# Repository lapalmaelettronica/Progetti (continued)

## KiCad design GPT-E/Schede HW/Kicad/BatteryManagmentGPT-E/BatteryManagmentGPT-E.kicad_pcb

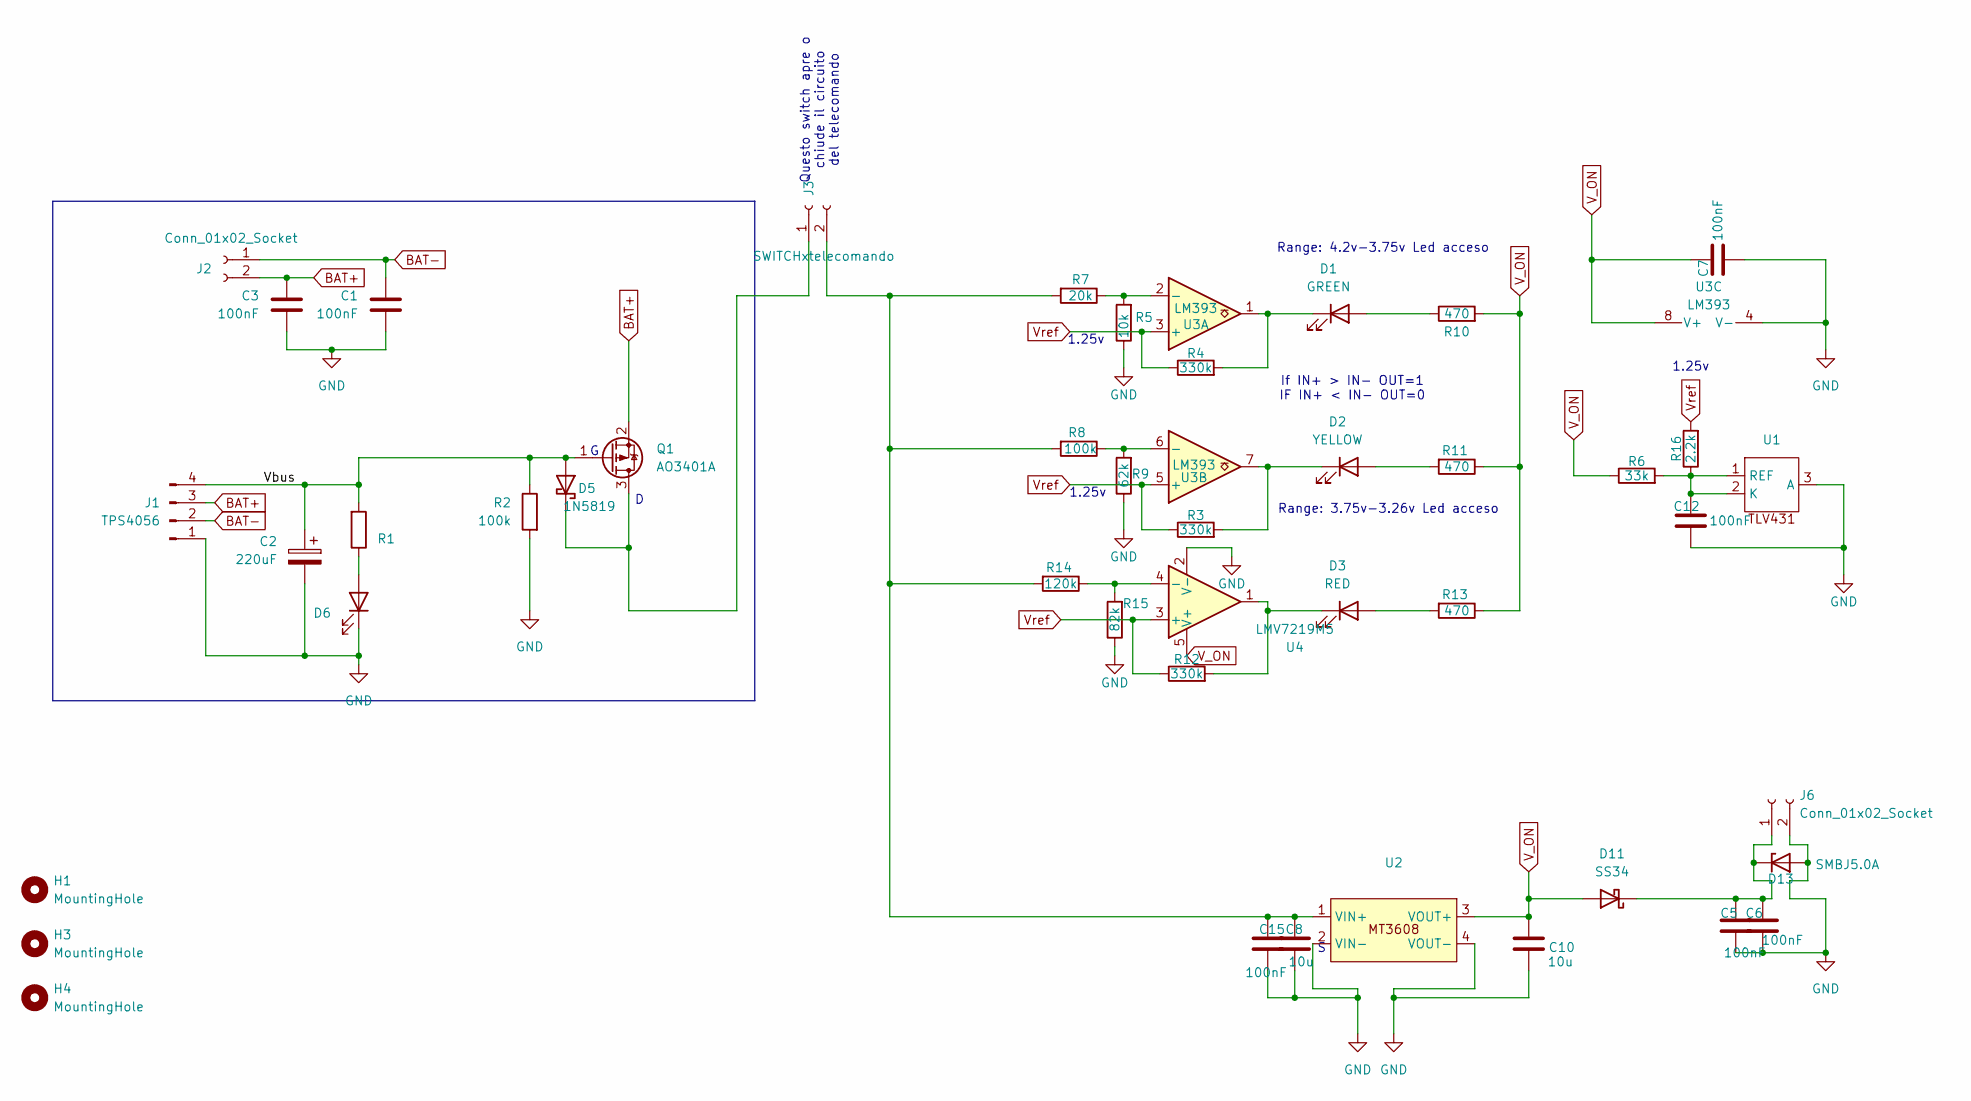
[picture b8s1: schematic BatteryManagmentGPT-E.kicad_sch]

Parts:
C1, C3, C5, C6, C7, C12, C15: 100nF; C_Disc_D4.3mm_W1.9mm_P5.00mm
C2: 220uF; CP_Radial_D5.0mm_P2.00mm
C8, C10: 10u; C_Disc_D4.3mm_W1.9mm_P5.00mm
D1: GREEN; LED_D4.0mm
D2: YELLOW; LED_D4.0mm
D3: RED; LED_D4.0mm
D5: 1N5819; D_DO-41_SOD81_P7.62mm_Horizontal
D6: LED; LED_D4.0mm
D11: SS34; D_SMB_Handsoldering
D13: SMBJ5.0A; D_SMB_Handsoldering
H1, H3, H4: MountingHole; MountingHole_2.2mm_M2
J1: TPS4056; Molex_KK-254_AE-6410-04A_1x04_P2.54mm_Vertical
J2, J6: Conn_01x02_Socket; TE_440054-2_1x02_P2.00mm_Vertical
J3: SWITCHxtelecomando; PinHeader_1x02_P2.54mm_Vertical
Q1: AO3401A; SOT-23
R1, R10, R11, R13: 470; R_Axial_DIN0204_L3.6mm_D1.6mm_P5.08mm_Horizontal
R2, R8: 100k; R_Axial_DIN0204_L3.6mm_D1.6mm_P5.08mm_Horizontal
R3, R4, R12: 330k; R_Axial_DIN0204_L3.6mm_D1.6mm_P5.08mm_Horizontal
R5: 10k; R_Axial_DIN0204_L3.6mm_D1.6mm_P5.08mm_Horizontal
R6: 33k; R_Axial_DIN0204_L3.6mm_D1.6mm_P5.08mm_Horizontal
R7: 20k; R_Axial_DIN0204_L3.6mm_D1.6mm_P5.08mm_Horizontal
R9: 62k; R_Axial_DIN0204_L3.6mm_D1.6mm_P5.08mm_Horizontal
R14: 120k; R_Axial_DIN0204_L3.6mm_D1.6mm_P5.08mm_Horizontal
R15: 82k; R_Axial_DIN0204_L3.6mm_D1.6mm_P5.08mm_Horizontal
R16: 2.2k; R_Axial_DIN0204_L3.6mm_D1.6mm_P5.08mm_Horizontal
U1: SOT-23-3
U2: MT3608-Module
U3: LM393; DIP-8_W7.62mm
U4: LMV7219M5; SOT-23-5_HandSoldering

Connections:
/Vbus: C2.1, D5.2 (A), J1.4, Q1.1 (G), R1.2, R2.1
BAT+: C3.1, J1.3, J2.2, Q1.2 (S)
BAT-: C1.1, J1.2, J2.1
GND: C1.2, C2.2, C3.2, C5.2, C6.2, C7.2, C8.2, C10.2, C12.2, C15.2, D6.1 (K), D13.2 (A), J1.1, J6.2, R2.2, R5.1, R9.1, R15.1, U1.3 (A), U2.2 (VIN-), U2.4 (VOUT-), U3.4 (V-), U4.2 (V-)
unnamed: D1.2 (A), R10.1
unnamed: D1.1 (K), R4.2, U3.1
unnamed: D2.2 (A), R11.2
unnamed: D2.1 (K), R3.2, U3.7
unnamed: D3.2 (A), R13.2
unnamed: D3.1 (K), R12.2, U4.1
unnamed: D5.1 (K), J3.1, Q1.3 (D)
unnamed: D6.2 (A), R1.1
unnamed: C5.1, C6.1, D11.1 (K), D13.1 (K), J6.1
unnamed: C8.1, C15.1, J3.2, R7.2, R8.2, R14.2, U2.1 (VIN+)
unnamed: C12.1, R6.2, R16.1, U1.1 (REF), U1.2 (K)
unnamed: R5.2, R7.1, U3.2 (-)
unnamed: R8.1, R9.2, U3.6 (-)
unnamed: R14.1, R15.2, U4.4 (-)
V_ON: C7.1, C10.1, D11.2 (A), R6.1, R10.2, R11.1, R13.1, U2.3 (VOUT+), U3.8 (V+), U4.5 (V+)
Vref: R3.1, R4.1, R12.1, R16.2, U3.3 (+), U3.5 (+), U4.3 (+)

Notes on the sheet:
If IN+ > IN- OUT=1 IF IN+ < IN- OUT=0
Range: 4.2v-3.75v Led acceso
1.25v
Range: 3.75v-3.26v Led acceso
Questo switch apre o chiude il circuito del telecomando

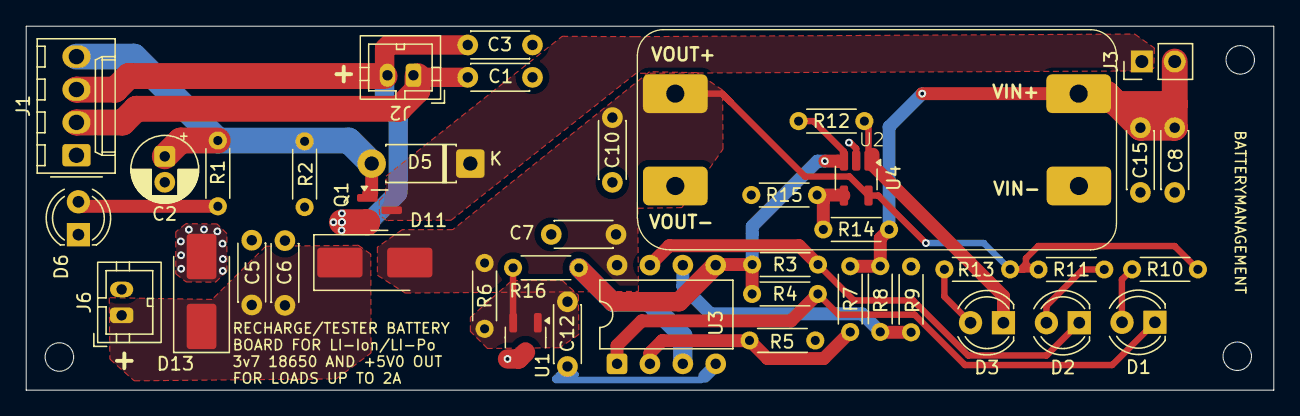
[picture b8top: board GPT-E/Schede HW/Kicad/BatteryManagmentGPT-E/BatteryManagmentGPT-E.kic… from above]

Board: 2 copper layers, 96.3 x 28.1 mm, 45 parts (0 on the bottom side), 20 nets.

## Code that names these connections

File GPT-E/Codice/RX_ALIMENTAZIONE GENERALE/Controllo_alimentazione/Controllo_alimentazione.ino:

#include <SPI.h>
#include <nRF24L01.h>
#include <RF24.h>

// ==========================================
// POWER MANAGEMENT GPT-E - ATmega8 + NRF24
// Ricevitore semplice, senza sleep/IRQ
// ==========================================

#define ENABLE_PIN 8    // PB0
#define CE_PIN     9    // PB1
#define CSN_PIN    10   // PB2
#define BUZZER     7    // PD7

RF24 radio(CE_PIN, CSN_PIN);

const byte address[6] = "ROB01";

#define CMD_POWER 10

struct RadioPacket {
  uint8_t type;
  uint8_t value;
};

bool robotPower = false;

void beep(unsigned int duration, uint8_t repetitions) {
  for (uint8_t i = 0; i < repetitions; i++) {
    digitalWrite(BUZZER, HIGH);
    delay(duration);
    digitalWrite(BUZZER, LOW);

    if (i < repetitions - 1) {
      delay(duration);
    }
  }
}

void setPower(bool state) {
  robotPower = state;

  if (state) {
    digitalWrite(ENABLE_PIN, HIGH);   // Q1 ON -> P-MOS ON
    beep(150, 2);                     // doppio bip = ON
  } else {
    digitalWrite(ENABLE_PIN, LOW);    // Q1 OFF -> P-MOS OFF
    beep(600, 1);                     // bip lungo = OFF
  }
}

void setup() {
  pinMode(ENABLE_PIN, OUTPUT);
  pinMode(BUZZER, OUTPUT);

  digitalWrite(ENABLE_PIN, LOW);
  digitalWrite(BUZZER, LOW);

  delay(200);

  if (!radio.begin()) {
    while (true) {
      beep(80, 5);   // errore NRF
      delay(1000);
    }
  }

  radio.setPALevel(RF24_PA_LOW);
  radio.setDataRate(RF24_1MBPS);
  radio.setChannel(76);

  radio.openReadingPipe(0, address);
  radio.startListening();

  beep(100, 1); // sistema pronto
}

void loop() {
  if (radio.available()) {
    RadioPacket packet;

    radio.read(&packet, sizeof(packet));

    if (packet.type == CMD_POWER) {
      if (packet.value == 1 && !robotPower) {
        setPower(true);
      }
      else if (packet.value == 0 && robotPower) {
        setPower(false);
      }
      else {
        // comando valido ma stato già uguale
        beep(40, 1);
      }
    }
  }
}

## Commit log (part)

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2026-01-13 GPT-E added!
2026-04-23 aggiunti file .step e .stl meccanica
